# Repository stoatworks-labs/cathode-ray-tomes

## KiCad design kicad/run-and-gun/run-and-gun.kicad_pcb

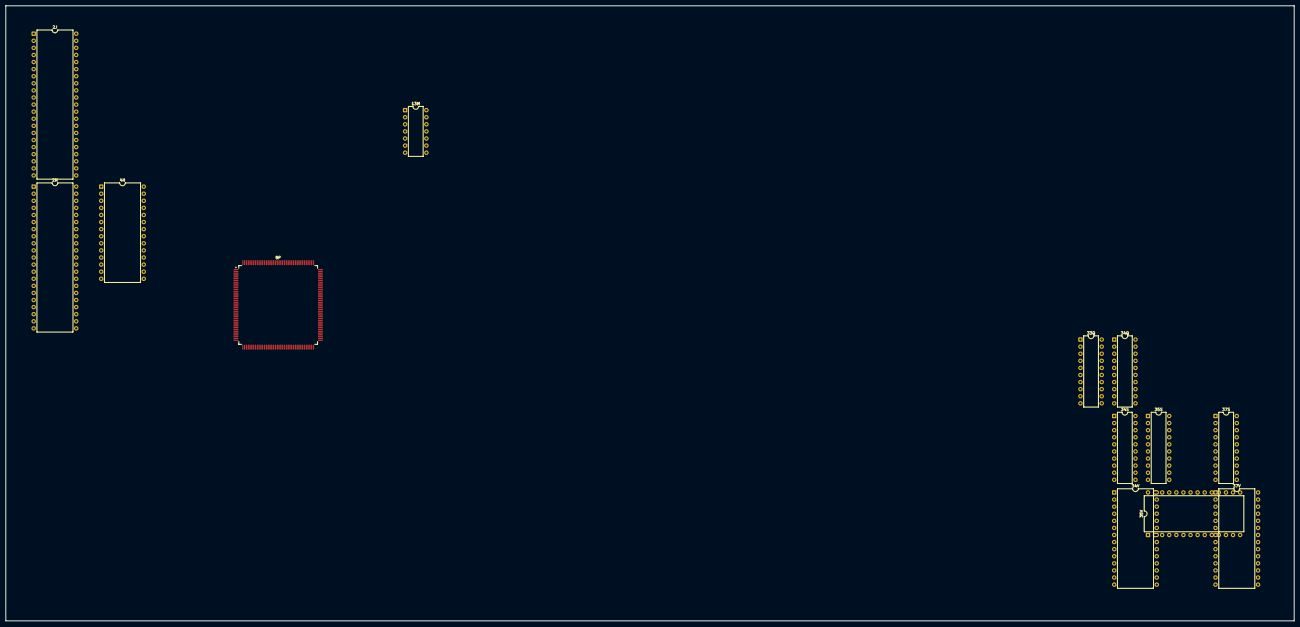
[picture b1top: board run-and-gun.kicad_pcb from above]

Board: 2 copper layers, 461.7 x 220.4 mm, 13 parts (0 on the bottom side), 98 nets, no tracks yet.

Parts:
2J, 2N: HN624116P; DIP-42_W15.24mm
4N: HM62256BLP; DIP-28_W15.24mm
8P: 054539; PQFP-160_28x28mm_P0.65mm
13M: 74LS04; DIP-14_W7.62mm
33Q: 74LS273; DIP-20_W7.62mm
34Q: 74LS244; DIP-20_W7.62mm
34S, 35S, 37S: 74LS245; DIP-20_W7.62mm
34V, 35V, 37V: CXK58257ASP-70L; DIP-28_W15.24mm

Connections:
/PSAC/A0: 34V.10, 35V.10, 37V.10
/PSAC/A1: 34V.9, 35V.9, 37V.9
/PSAC/A2: 34V.8, 35V.8, 37V.8
/PSAC/A3: 34V.7, 35V.7, 37V.7
/PSAC/A4: 34V.6, 35V.6, 37V.6
/PSAC/A5: 34V.5, 35V.5, 37V.5
/PSAC/A6: 34V.4, 35V.4, 37V.4
/PSAC/A7: 34V.3, 35V.3, 37V.3
/PSAC/A8: 34V.25, 35V.25, 37V.25
/PSAC/A9: 34V.24, 35V.24, 37V.24
/PSAC/A10: 34V.21, 35V.21, 37V.21
/PSAC/A11: 34V.23, 35V.23, 37V.23
/PSAC/A12: 34V.2, 35V.2, 37V.2
/PSAC/A13: 34V.26, 35V.26, 37V.26
/PSAC/A14: 34V.1, 35V.1, 37V.1
/PSAC/DIR: 34S.1, 35S.1, 37S.1
/PSAC/VDD: 34V.28, 35V.28, 37V.28
/PSAC/VSS: 34V.14, 35V.14, 37V.14
/PSAC/X0: 33Q.4, 34Q.2
/PSAC/X1: 33Q.8, 34Q.4
/PSAC/X2: 33Q.14, 34Q.6
/PSAC/X3: 33Q.18, 34Q.8
/PSAC/X4: 33Q.3, 34Q.11
/PSAC/X5: 33Q.7, 34Q.13
/PSAC/X6: 33Q.13, 34Q.15
/PSAC/X7: 33Q.17, 34Q.17
/PSAC/~CS: 34V.20, 35V.20, 37V.20
/PSAC/~OE: 34V.22, 35V.22, 37V.22
/pcm/K054539/RAMR~W: 4N.27, 8P.107
/pcm/K054539/RAM~CE: 4N.20, 8P.109
/pcm/K054539/RAM~OE: 4N.22, 8P.108
/pcm/K054539/ROM~CE: 2J.11, 2N.11, 8P.133
/pcm/K054539/ROM~OE: 2N.13, 8P.131, 13M.11
/pcm/K054539/R_A0: 2N.30, 4N.10, 8P.132
/pcm/K054539/R_A1: 2J.10, 2N.10, 4N.9, 8P.135
/pcm/K054539/R_A2: 2J.9, 2N.9, 4N.8, 8P.137
/pcm/K054539/R_A3: 2J.8, 2N.8, 4N.7, 8P.141
/pcm/K054539/R_A4: 2J.7, 2N.7, 4N.6, 8P.143
/pcm/K054539/R_A5: 2J.6, 2N.6, 4N.5, 8P.146
/pcm/K054539/R_A6: 2J.5, 2N.5, 4N.4, 8P.148
/pcm/K054539/R_A7: 2J.4, 2N.4, 4N.3, 8P.151
/pcm/K054539/R_A8: 2J.3, 2N.3, 4N.25, 8P.153
/pcm/K054539/R_A9: 2J.41, 2N.41, 4N.24, 8P.157
/pcm/K054539/R_A10: 2J.40, 2N.40, 4N.21, 8P.154
/pcm/K054539/R_A11: 2J.39, 2N.39, 4N.23, 8P.152
/pcm/K054539/R_A12: 2J.38, 2N.38, 4N.2, 8P.149
/pcm/K054539/R_A13: 2J.37, 2N.37, 4N.26, 8P.147
/pcm/K054539/R_A14: 2J.36, 2N.36, 8P.144
/pcm/K054539/R_A15: 2J.35, 2N.35, 8P.142
/pcm/K054539/R_A16: 2J.34, 2N.34, 4N.1, 8P.138
/pcm/K054539/R_A17: 2J.33, 2N.33, 8P.136
/pcm/K054539/R_A18: 2J.2, 2N.2, 8P.156
/pcm/K054539/R_A19: 2J.1, 2N.1, 8P.158
/pcm/K054539/R_A20: 2J.42, 2N.42, 8P.159
/pcm/K054539/R_D0: 2J.14, 2N.14, 4N.11, 8P.128
/pcm/K054539/R_D1: 2J.16, 2N.16, 4N.12, 8P.126
/pcm/K054539/R_D2: 2J.18, 2N.18, 4N.13, 8P.124
/pcm/K054539/R_D3: 2J.20, 2N.20, 4N.15, 8P.122
/pcm/K054539/R_D4: 2J.23, 2N.23, 4N.16, 8P.123
/pcm/K054539/R_D5: 2J.25, 2N.25, 4N.17, 8P.125
/pcm/K054539/R_D6: 2J.27, 2N.27, 4N.18, 8P.127
/pcm/K054539/R_D7: 2J.29, 2N.29, 4N.19, 8P.129
GND: 33Q.10, 34Q.10
unnamed: 2J.13, 13M.10
unnamed: 34Q.18, 37S.2
unnamed: 34Q.9, 37S.6
unnamed: 34Q.16, 37S.3
unnamed: 34Q.7, 37S.7
unnamed: 34Q.14, 37S.4
unnamed: 34Q.5, 37S.8
unnamed: 34Q.12, 37S.5
unnamed: 34Q.3, 37S.9
unnamed: 34S.18, 34V.11
unnamed: 34S.17, 34V.12
unnamed: 34S.16, 34V.13
unnamed: 34S.15, 34V.15
unnamed: 34S.14, 34V.16
unnamed: 34S.13, 34V.17
unnamed: 34S.12, 34V.18
unnamed: 34S.11, 34V.19
unnamed: 35S.18, 35V.11
unnamed: 35S.17, 35V.12
unnamed: 35S.16, 35V.13
unnamed: 35S.15, 35V.15
unnamed: 35S.14, 35V.16
unnamed: 35S.13, 35V.17
unnamed: 35S.12, 35V.18
unnamed: 35S.11, 35V.19
unnamed: 37S.18, 37V.11
unnamed: 37S.17, 37V.12
unnamed: 37S.16, 37V.13
unnamed: 37S.15, 37V.15
unnamed: 37S.14, 37V.16
unnamed: 37S.13, 37V.17
unnamed: 37S.12, 37V.18
unnamed: 37S.11, 37V.19
VCC: 2J.22, 2N.22, 4N.28, 8P.20, 8P.40, 8P.56, 8P.60, 8P.73, 8P.80, 8P.100, 8P.120, 8P.140, 8P.160, 33Q.20, 34Q.20
VSS: 2J.12, 2J.31, 2J.32, 2N.12, 2N.31, 2N.32, 8P.1, 8P.10, 8P.30, 8P.41, 8P.50, 8P.57, 8P.59, 8P.61, 8P.62, 8P.65, 8P.66, 8P.70, 8P.72, 8P.74, 8P.81, 8P.90, 8P.110, 8P.121, 8P.130, 8P.139, 8P.150

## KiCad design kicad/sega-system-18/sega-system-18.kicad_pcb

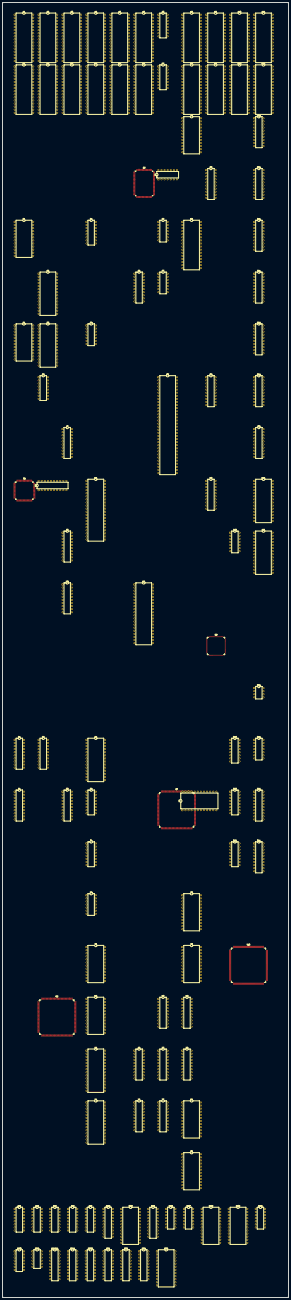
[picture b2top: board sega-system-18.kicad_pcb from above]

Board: 2 copper layers, 235.2 x 1065.0 mm, 114 parts (0 on the bottom side), 662 nets, no tracks yet.

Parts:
A1, A2, A3, A5, A6, A8, A9, A10, A11: 27C020; DIP-32_W15.24mm
A4: 27C010; DIP-32_W15.24mm
A7: 2501; DIP-16_W7.62mm
AA4, AA5, AA6, AA8, AA9: 2501; DIP-16_W7.62mm
AA11: 74LS245; DIP-20_W7.62mm
B1, B2, B3, B4, B5, B6, B8, B9, B10, B11: 27C020; DIP-32_W15.24mm
B7: 74LS139; DIP-16_W7.62mm
BB8: HM6116P-3; DIP-24_W15.24mm
BB9: 74LS245; DIP-20_W7.62mm
C8: HM6116P-3; DIP-24_W15.24mm
C11: 74LS244; DIP-20_W7.62mm
D6: 315_5296; PQFP-100_14x20mm_P0.65mm
D7: 74LS08; DIP-14_W7.62mm
D9: 74LS245; DIP-20_W7.62mm
D11: 74LS244; DIP-20_W7.62mm
E1: YM3438; DIP-24_W15.24mm
E4: 74LS157; DIP-16_W7.62mm
E7: 7400; DIP-14_W7.62mm
E8: 315-5242; DIP-32_W15.24mm
E11: 74LS374; DIP-20_W7.62mm
F2: HM65256B_SERIES; DIP-28_W15.24mm
F6: 74LS273; DIP-20_W7.62mm
F7: 74LS32; DIP-14_W7.62mm
F11: 74LS374; DIP-20_W7.62mm
G1: YM3438; DIP-24_W15.24mm
G2: HM65256B_SERIES; DIP-28_W15.24mm
G4: 74LS32; DIP-14_W7.62mm
G11: 74LS244; DIP-20_W7.62mm
H2: 74LS139; DIP-16_W7.62mm
H7: 68000D; DIP-64_W15.24mm
H9: 74LS245; DIP-20_W7.62mm
H11: 74LS244; DIP-20_W7.62mm
IC66, IC67: 74HC4066; DIP-14_W7.62mm
IC69, IC70: MB8461-12; DIP-24_W15.24mm
IC92, IC93: TL084; DIP-14_W7.62mm
IC94: MB3733-31; DIP-12_W7.62mm
J3: PAL16L8; DIP-20_W7.62mm
J11: 74LS244; DIP-20_W7.62mm
K1: ASSP5C68A; PQFP-80_14x14mm_P0.65mm
K2, K9: 74LS245; DIP-20_W7.62mm
K4: Z80CPU; DIP-40_W15.24mm
K11: MB8464A-10L-LL; DIP-28_W15.24mm
L3: 74LS244; DIP-20_W7.62mm
L10: 74LS74; DIP-14_W7.62mm
L11: MB8464A-10L-LL; DIP-28_W15.24mm
M3: 74LS244; DIP-20_W7.62mm
M6: D8751H-8; DIP-40_W15.24mm
N9: 315-5360; TQFP-120_14x14mm_P0.4mm
P11: MB3771; DIP-8_W7.62mm
PALR11: PAL16R6; DIP-20_W7.62mm
PD11: PLUS153DN; DIP-20_W7.62mm
PRR8: PAL16L8; DIP-20_W7.62mm
Q1, Q2: 74LS244; DIP-20_W7.62mm
Q4: TMM2063AP_10; DIP-28_W15.24mm
Q10: 74F367; DIP-16_W7.62mm
Q11: 74LS74; DIP-14_W7.62mm
RR1, RR2: 74LS374; DIP-20_W7.62mm
RR4: 74LS273; DIP-20_W7.62mm
RR8: CY7C128-45PC; DIP-24_W15.24mm
S1: 74LS373; DIP-20_W7.62mm
S3: 74LS374; DIP-20_W7.62mm
S4: 74LS157; DIP-16_W7.62mm
S7: 315-5361; PQFP-160_28x28mm_P0.65mm
S8: CY7C128-45PC; DIP-24_W15.24mm
S10: 74F163; DIP-16_W7.62mm
S11: PAL16L8; DIP-20_W7.62mm
T4: 74LS157; DIP-16_W7.62mm
T10: 74F163; DIP-16_W7.62mm
T11: PAL16L8; DIP-20_W7.62mm
U4: 74LS74; DIP-14_W7.62mm
U8: CY7C128-45PC; DIP-24_W15.24mm
V4: HM6116P-3; DIP-24_W15.24mm
V8: CY7C128-45PC; DIP-24_W15.24mm
V10: 315-5313; PQFP-128_28x28mm_P0.8mm
W2: 315-5362; PQFP-160_28x28mm_P0.65mm
W4: HM6116P-3; DIP-24_W15.24mm
W7: 74LS245; DIP-20_W7.62mm
W8: 74LS244; DIP-20_W7.62mm
X4: HM65256B_SERIES; DIP-28_W15.24mm
X6, X8: 74LS244; DIP-20_W7.62mm
X7: 74LS245; DIP-20_W7.62mm
Y4: HM65256B_SERIES; DIP-28_W15.24mm
Y6, Y7: 74LS244; DIP-20_W7.62mm
Y8: CY7C128-45PC; DIP-24_W15.24mm
Z8: CY7C128-45PC; DIP-24_W15.24mm

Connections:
/BUFFOBJ~OE: W8.1, W8.19, X8.1, X8.19
/BUFFSH_A->B: S7.159, W7.1, X7.1
/CLK8: D6.85, E1.24, E7.9, E7.10, G1.24, K4.6, M6.19, Q10.10, Q11.5, U4.3
/COLA0: BB8.8, C8.8, C11.5, W2.58
/COLA1: BB8.7, C8.7, C11.7, W2.57
/COLA2: BB8.6, C8.6, C11.3, W2.56
/COLA3: BB8.5, C8.5, D11.18, W2.54
/COLA4: BB8.4, C8.4, D11.16, W2.53
/COLA5: BB8.3, C8.3, D11.14, W2.52
/COLA6: BB8.2, C8.2, D11.12, W2.51
/COLA7: BB8.1, C8.1, D11.9, W2.49
/COLA8: BB8.23, C8.23, D11.7, W2.48
/COLA9: BB8.22, C8.22, D11.5, W2.47
/COLA10: BB8.19, C8.19, D11.3, W2.46
/Color Mixer/COLAD0: C8.9, D9.11, E8.10
/Color Mixer/COLAD1: C8.10, D9.12, E8.11
/Color Mixer/COLAD2: C8.11, D9.13, E8.12
/Color Mixer/COLAD3: C8.13, D9.14, E8.13
/Color Mixer/COLAD4: C8.14, D9.15, E8.23
/Color Mixer/COLAD5: C8.15, D9.16, E8.22
/Color Mixer/COLAD6: C8.16, D9.17, E8.21
/Color Mixer/COLAD7: C8.17, D9.18, E8.20
/Color Mixer/COLAD8: BB8.9, BB9.11, E8.4
/Color Mixer/COLAD9: BB8.10, BB9.12, E8.5
/Color Mixer/COLAD10: BB8.11, BB9.13, E8.6
/Color Mixer/COLAD11: BB8.13, BB9.14, E8.7
/Color Mixer/COLAD12: BB8.14, BB9.15, E8.9
/Color Mixer/COLAD13: BB8.15, BB9.16, E8.25
/Color Mixer/COLAD14: BB8.16, BB9.17, E8.3
/Color Mixer/COLAD15: BB8.17, BB9.18
/Color Mixer/S18B: E8.31, IC66.8
/Color Mixer/S18G: E8.18, IC66.4
/Color Mixer/S18R: E8.15, IC66.1
/Color Mixer/video_mux/OBJPRIO0': E11.5, PD11.7
/Color Mixer/video_mux/OBJPRIO1': F11.19, PD11.6
/Color Mixer/video_mux/PRIO0: F6.2, PD11.17
/Color Mixer/video_mux/PRIO1: F6.5, PD11.16
/Color Mixer/video_mux/PRIO2: F6.6, PD11.15
/Color Mixer/video_mux/PRIO3: F6.9, PD11.14
/Color Mixer/video_mux/TILEMAP0': F11.5, PD11.3
/Color Mixer/video_mux/TILEMAP1': F11.9, PD11.4
/Color Mixer/video_mux/TILEMAP3': E11.9, PD11.8
/Color Mixer/video_mux/TILEMAP4': E11.15, PD11.9
/Color Mixer/video_mux/VDP_SEL: IC67.5, IC67.6, IC67.12, IC67.13, PD11.18
/Color Mixer/video_mux/~SA': F11.15, PD11.5
/Color Mixer/video_mux/~VDP_SEL: IC66.5, IC66.6, IC66.12, IC66.13, PD11.19
/Color Mixer/~WR_H: C8.21, C11.9
/Color Mixer/~WR_L: BB8.21, C11.12
/DC_SND~CS: K1.77, PRR8.4
/EDCK: PALR11.18, V10.53
/FC0: H7.28, N9.116
/FC1: H7.27, N9.115
/FLIP: D6.3, PRR8.6, S7.158, W2.128
/IO Controller/GPIO0: AA11.2, D6.33
/IO Controller/GPIO1: AA11.3, D6.32
/IO Controller/GPIO2: AA11.4, D6.31
/IO Controller/GPIO3: AA11.5, D6.30
/IO Controller/GPIO4: AA11.6, D6.29
/IO Controller/GPIO5: AA11.7, D6.28
/IO Controller/GPIO6: AA11.8, D6.27
/IO Controller/GPIO7: AA11.9, D6.26
/IO Controller/IO_1P_BTN_1: AA8.14, D6.17
/IO Controller/IO_1P_BTN_2: AA8.16, D6.18
/IO Controller/IO_1P_BTN_3: AA8.12, D6.19
/IO Controller/IO_1P_BTN_4: AA8.10, D6.20
/IO Controller/IO_1P_DOWN: AA9.16, D6.21
/IO Controller/IO_1P_LEFT: AA9.12, D6.24
/IO Controller/IO_1P_RIGHT: AA9.10, D6.23
/IO Controller/IO_1P_UP: AA9.14, D6.22
/IO Controller/IO_2P_BTN_1: AA6.14, D6.7
/IO Controller/IO_2P_BTN_2: AA6.16, D6.8
/IO Controller/IO_2P_BTN_3: AA6.12, D6.9
/IO Controller/IO_2P_BTN_4: AA6.10, D6.10
/IO Controller/IO_2P_DOWN: A7.16, D6.11
/IO Controller/IO_2P_LEFT: A7.12, D6.14
/IO Controller/IO_2P_RIGHT: A7.10, D6.13
/IO Controller/IO_2P_UP: A7.14, D6.12
/IO Controller/IO_A-B: AA11.1, D6.34
/IO Controller/IO_DRIVER1: D6.86, F7.4, F7.9
/IO Controller/SCRA_A15: D6.88, E4.2
/IO Controller/SCRA_A16: D6.89, E4.5
/IO Controller/SCRA_A17: D6.93, E4.11
/IO Controller/SCRA_A18: D6.92, E4.14
/IO Controller/SCRB_A15: D6.94, E4.3
/IO Controller/SCRB_A16: D6.95, E4.6
/IO Controller/SCRB_A17: D6.97, E4.10
/IO Controller/SCRB_A18: D6.96, E4.13
/IO Controller/~AB12: E7.11, F7.10
/IO_1P_SELECT: AA5.12, D6.44, M6.8
/IO_1P_START: AA5.14, D6.42, M6.6
/IO_2P_SELECT: AA5.10, D6.43, M6.7
/IO_2P_START: AA5.16, D6.39, M6.5
/IO_COIN_1: AA4.14, D6.35, M6.1
/IO_COIN_2: AA4.16, D6.36, M6.2
/IO_COIN_3: AA4.12, D6.37, M6.3
/IO_SERVICE: AA4.10, D6.38, M6.4
/MAIN_A1: C11.15, G11.8, H7.29, N9.6
/MAIN_A2: C11.13, G11.13, H7.30, N9.7
/MAIN_A3: C11.17, G11.6, H7.31, N9.8
/MAIN_A4: D11.2, G11.15, H7.32, N9.9
/MAIN_A5: D11.4, G11.4, H7.33, N9.10
/MAIN_A6: D11.6, G11.17, H7.34, N9.11
/MAIN_A7: D11.8, G11.2, H7.35, N9.12
/MAIN_A8: D11.11, H7.36, H11.11, N9.13
/MAIN_A9: D11.13, H7.37, H11.8, N9.16
/MAIN_A10: D11.15, H7.38, H11.13, N9.17
/MAIN_A11: D11.17, H7.39, H11.6, N9.18
/MAIN_A12: H7.40, H11.15, N9.19
/MAIN_A13: H7.41, H11.4, N9.20
/MAIN_A14: H7.42, H11.17, N9.21
/MAIN_A15: H7.43, H11.2, N9.22
/MAIN_A16: H7.44, J11.11, N9.23
/MAIN_A17: H7.45, J11.8, N9.5
/MAIN_A18: H7.46, J11.13, N9.4
/MAIN_A19: H7.47, J11.6, N9.3
/MAIN_A20: H7.48, J11.15, N9.2
/MAIN_A21: H7.50, J11.4, N9.119
/MAIN_A22: H7.51, J11.17, N9.118
/MAIN_A23: H7.52, J11.2, N9.117
/MAIN_AB1: A5.12, A6.12, D6.81, G11.12, K11.10, L11.10, S7.1, V10.71, Y6.2
/MAIN_AB2: A5.11, A6.11, D6.80, G11.7, K11.9, L11.9, S7.2, V10.72, Y6.4
/MAIN_AB3: A5.10, A6.10, D6.79, G11.14, K11.8, L11.8, V10.73, Y6.6, Y7.8
/MAIN_AB4: A5.9, A6.9, D6.78, G11.5, K11.7, L11.7, V10.74, Y6.8, Y7.11
/MAIN_AB5: A5.8, A6.8, D6.77, G11.16, K11.6, L11.6, V10.75, Y6.17, Y7.6
/MAIN_AB6: A5.7, A6.7, G11.3, K11.5, L11.5, V10.76, Y6.15, Y7.13
/MAIN_AB7: A5.6, A6.6, G11.18, K11.4, L11.4, V10.77, Y6.13, Y7.4
/MAIN_AB8: A5.5, A6.5, H11.9, K11.3, L11.3, V10.78, Y6.11, Y7.15
/MAIN_AB9: A5.27, A6.27, H11.12, K11.25, L11.25, V10.79, X6.11, Y7.2
/MAIN_AB10: A5.26, A6.26, H11.7, K11.24, L11.24, V10.80, X6.13, Y7.17
/MAIN_AB11: A5.23, A6.23, H11.14, K11.21, L11.21, V10.81, X6.15
/MAIN_AB12: A5.25, A6.25, E7.13, F7.5, H11.5, K11.23, L11.23, V10.82, X6.8
/MAIN_AB13: A5.4, A6.4, D6.62, H11.16, K11.2, L11.2, V10.83, X6.6
/MAIN_AB14: A5.28, A6.28, H11.3, V10.84, X6.4
/MAIN_AB15: A5.29, A6.29, H11.18, V10.85, X6.2
/MAIN_AB16: A5.3, A6.3, J11.9, V10.86, W2.152
/MAIN_AB17: A5.2, A6.2, J11.12, V10.87
/MAIN_AB18: A5.30, A6.30, J11.7, V10.88
/MAIN_AB19: J11.14, V10.89
/MAIN_AB20: J11.5, V10.90
/MAIN_AB21: J11.16, V10.91
/MAIN_AB22: J11.3, V10.92
/MAIN_AB23: J11.18, V10.93
/MAIN_CLK: H7.15, K1.70, L10.5, N9.106, Q10.6, V10.49
/MAIN_D0: D9.9, F6.3, H7.5, H9.2, N9.76, Q1.11, RR1.12
/MAIN_D1: D9.8, F6.4, H7.4, H9.3, N9.77, Q1.8, RR1.9
/MAIN_D2: D9.7, F6.7, H7.3, H9.4, N9.78, Q1.13, RR1.15
/MAIN_D3: D9.6, F6.8, H7.2, H9.5, N9.79, Q1.6, RR1.6
/MAIN_D4: D9.5, F6.13, H7.1, H9.6, N9.80, Q1.15, RR1.16
/MAIN_D5: D9.4, F6.14, H7.64, H9.7, N9.81, Q1.4, RR1.5
/MAIN_D6: D9.3, F6.17, H7.63, H9.8, N9.82, Q1.17, RR1.19
/MAIN_D7: D9.2, F6.18, H7.62, H9.9, N9.83, Q1.2, RR1.2
/MAIN_D8: BB9.9, H7.61, K9.2, N9.86, Q2.11, RR2.12
/MAIN_D9: BB9.8, H7.60, K9.3, N9.87, Q2.8, RR2.9
/MAIN_D10: BB9.7, H7.59, K9.4, N9.88, Q2.13, RR2.15
/MAIN_D11: BB9.6, H7.58, K9.5, N9.89, Q2.6, RR2.6
/MAIN_D12: BB9.5, H7.57, K9.6, N9.90, Q2.15, RR2.16
/MAIN_D13: BB9.4, H7.56, K9.7, N9.92, Q2.4, RR2.5
/MAIN_D14: BB9.3, H7.55, K9.8, N9.93, Q2.17, RR2.19
/MAIN_D15: BB9.2, H7.54, K9.9, N9.94, Q2.2, RR2.2
/MAIN_DB0: A5.13, D6.74, H9.18, L11.11, V10.55, X7.2
/MAIN_DB1: A5.14, D6.73, H9.17, L11.12, V10.56, X7.3
/MAIN_DB2: A5.15, D6.72, H9.16, L11.13, V10.57, X7.4
/MAIN_DB3: A5.17, D6.71, H9.15, L11.15, V10.58, X7.5
/MAIN_DB4: A5.18, D6.70, H9.14, L11.16, V10.59, X7.6
/MAIN_DB5: A5.19, D6.69, H9.13, L11.17, V10.60, X7.7
/MAIN_DB6: A5.20, D6.68, H9.12, L11.18, V10.61, X7.8
/MAIN_DB7: A5.21, D6.67, H9.11, L11.19, V10.62, X7.9
/MAIN_DB8: A6.13, K9.18, K11.11, V10.63, W7.2
/MAIN_DB9: A6.14, K9.17, K11.12, V10.64, W7.3
/MAIN_DB10: A6.15, K9.16, K11.13, V10.65, W7.4
/MAIN_DB11: A6.17, K9.15, K11.15, V10.66, W7.5
/MAIN_DB12: A6.18, K9.14, K11.16, V10.67, W7.6
/MAIN_DB13: A6.19, K9.13, K11.17, V10.68, W7.7
/MAIN_DB14: A6.20, K9.12, K11.18, V10.69, W7.8
/MAIN_DB15: A6.21, K9.11, K11.19, V10.70, W7.9
/MAIN_R~W: H7.9, N9.99, V10.113
/MAIN_~CE: A5.22, A6.22, N9.70
/MAIN_~OE: A5.24, A6.24, D6.82, K11.22, L11.22, N9.41
/MAIN_~RD: BB9.1, D6.84, D9.1, H9.1, K9.1, N9.49
/MAIN_~WR: D6.83, F7.2, L11.27
/MAIN~HALT: H7.17, N9.107
/MAIN~RST: H7.18, N9.108
/MAPP2MAIN~WE: K11.27, N9.42
/MMAP_~DRI5: N9.47, W2.148
/MegaDrive VDP/A0: IC69.23, IC70.23
/MegaDrive VDP/A1: IC69.22, IC70.22
/MegaDrive VDP/A2: IC69.21, IC70.21
/MegaDrive VDP/A3: IC69.20, IC70.20
/MegaDrive VDP/A4: IC69.17, IC70.17
/MegaDrive VDP/A5: IC69.16, IC70.16
/MegaDrive VDP/A6: IC69.15, IC70.15
/MegaDrive VDP/A7: IC69.19, IC70.19
/MegaDrive VDP/AD0: IC69.11, V10.31
/MegaDrive VDP/AD1: IC69.12, V10.32
/MegaDrive VDP/AD2: IC69.1, V10.33
/MegaDrive VDP/AD3: IC69.2, V10.34
/MegaDrive VDP/AD4: IC70.11, V10.35
/MegaDrive VDP/AD5: IC70.12, V10.36
/MegaDrive VDP/AD6: IC70.1, V10.37
/MegaDrive VDP/AD7: IC70.2, V10.38
/MegaDrive VDP/~CAS: IC69.24, IC70.24
/MegaDrive VDP/~OE1: IC69.10, IC70.10, V10.16
/MegaDrive VDP/~RAS: IC69.14, IC70.14
/MegaDrive VDP/~SC: IC69.7, IC70.7, V10.11
/MegaDrive VDP/~SE0: IC69.3, IC70.3, V10.10
/MegaDrive VDP/~WE0: IC69.13, IC70.13, V10.15
/Memory Mapper/INT1: M6.13, N9.51
/Memory Mapper/PO_0: M6.39, N9.52
/Memory Mapper/PO_1: M6.38, N9.53
/Memory Mapper/PO_2: M6.37, N9.54
/Memory Mapper/PO_3: M6.36, N9.55
/Memory Mapper/PO_4: M6.35, N9.56
/Memory Mapper/PO_5: M6.34, N9.57
/Memory Mapper/PO_6: M6.33, N9.58
/Memory Mapper/PO_7: M6.32, N9.59
/Memory Mapper/UCRST: M6.9, Q11.8
/OBJCOL0: S7.79, W2.31
/OBJCOL1: S7.78, W2.32
/OBJCOL2: S7.77, W2.33
/OBJCOL3: S7.76, W2.34
/OBJCOL4: S7.75, W2.36
/OBJCOL5: S7.74, W2.37
/OBJCOL6: S7.73, W2.38
/OBJCOL7: S7.72, W2.39
/OBJCOL8: S7.71, W2.42
/OBJCOL9: S7.69, W2.43
/OBJCOL10: E11.3, S7.68, W2.44
/OBJCOL11: F11.17, S7.66, W2.45
/OBJCOL~UK0: S7.156, W2.153
/OBJCOL~UK1: S7.157, W2.154
/OBJ_A0: A8.12, A9.12, A10.12, A11.12, B8.12, B9.12, B10.12, B11.12, X8.9
/OBJ_A1: A8.11, A9.11, A10.11, A11.11, B8.11, B9.11, B10.11, B11.11, X8.12
/OBJ_A2: A8.10, A9.10, A10.10, A11.10, B8.10, B9.10, B10.10, B11.10, X8.7
/OBJ_A3: A8.9, A9.9, A10.9, A11.9, B8.9, B9.9, B10.9, B11.9, X8.14
/OBJ_A4: A8.8, A9.8, A10.8, A11.8, B8.8, B9.8, B10.8, B11.8, X8.5
/OBJ_A5: A8.7, A9.7, A10.7, A11.7, B8.7, B9.7, B10.7, B11.7, X8.16
/OBJ_A6: A8.6, A9.6, A10.6, A11.6, B8.6, B9.6, B10.6, B11.6, X8.3
/OBJ_A7: A8.5, A9.5, A10.5, A11.5, B8.5, B9.5, B10.5, B11.5, X8.18
/OBJ_A8: A8.27, A9.27, A10.27, A11.27, B8.27, B9.27, B10.27, B11.27, W8.9
/OBJ_A9: A8.26, A9.26, A10.26, A11.26, B8.26, B9.26, B10.26, B11.26, W8.12
/OBJ_A10: A8.23, A9.23, A10.23, A11.23, B8.23, B9.23, B10.23, B11.23, W8.7
/OBJ_A11: A8.25, A9.25, A10.25, A11.25, B8.25, B9.25, B10.25, B11.25, W8.14
/OBJ_A12: A8.4, A9.4, A10.4, A11.4, B8.4, B9.4, B10.4, B11.4, W8.5
/OBJ_A13: A8.28, A9.28, A10.28, A11.28, B8.28, B9.28, B10.28, B11.28, W8.16
/OBJ_A14: A8.29, A9.29, A10.29, A11.29, B8.29, B9.29, B10.29, B11.29, W8.3
/OBJ_A15: A8.3, A9.3, A10.3, A11.3, B8.3, B9.3, B10.3, B11.3, W8.18
/OBJ_D0: B8.13, B9.13, B10.13, B11.13, S7.81
/OBJ_D1: B8.14, B9.14, B10.14, B11.14, S7.82
/OBJ_D2: B8.15, B9.15, B10.15, B11.15, S7.83
/OBJ_D3: B8.17, B9.17, B10.17, B11.17, S7.84
/OBJ_D4: B8.18, B9.18, B10.18, B11.18, S7.85
/OBJ_D5: B8.19, B9.19, B10.19, B11.19, S7.86
/OBJ_D6: B8.20, B9.20, B10.20, B11.20, S7.87
/OBJ_D7: B8.21, B9.21, B10.21, B11.21, S7.89
/OBJ_D8: A8.13, A9.13, A10.13, A11.13, S7.91
/OBJ_D9: A8.14, A9.14, A10.14, A11.14, S7.92
/OBJ_D10: A8.15, A9.15, A10.15, A11.15, S7.93
/OBJ_D11: A8.17, A9.17, A10.17, A11.17, S7.95
/OBJ_D12: A8.18, A9.18, A10.18, A11.18, S7.96
/OBJ_D13: A8.19, A9.19, A10.19, A11.19, S7.98
/OBJ_D14: A8.20, A9.20, A10.20, A11.20, S7.99
/OBJ_D15: A8.21, A9.21, A10.21, A11.21, S7.101
/PCM_~CE0: B4.22, H2.5
/PCM_~CE1: B5.22, H2.6
/PCM_~CE2: B6.22, H2.7
/ROM board/OBJ_MSB0: A8.2, A9.2, A10.2, A11.2, B8.2, B9.2, B10.2, B11.2
/ROM board/OBJ_MSB1: A8.30, A9.30, A10.30, A11.30, B8.30, B9.30, B10.30, B11.30
/ROM board/PCM_SNDROM: B4.30, B5.30, B6.30
/ROM board/SCR_MSB: A1.30, A2.30, A3.30, B1.30, B2.30, B3.30
/ROM board/SCR_~OE: A1.2, A1.24, A2.2, A2.24, A3.2, A3.24, B1.2, B2.2, B3.2
/ROM board/cpurom/SND_AB0: A4.12, B4.12, B5.12, B6.12
/ROM board/cpurom/SND_AB1: A4.11, B4.11, B5.11, B6.11
/ROM board/cpurom/SND_AB2: A4.10, B4.10, B5.10, B6.10
/ROM board/cpurom/SND_AB3: A4.9, B4.9, B5.9, B6.9
/ROM board/cpurom/SND_AB4: A4.8, B4.8, B5.8, B6.8
/ROM board/cpurom/SND_AB5: A4.7, B4.7, B5.7, B6.7
/ROM board/cpurom/SND_AB6: A4.6, B4.6, B5.6, B6.6
/ROM board/cpurom/SND_AB7: A4.5, B4.5, B5.5, B6.5
/ROM board/cpurom/SND_AB8: A4.27, B4.27, B5.27, B6.27
/ROM board/cpurom/SND_AB9: A4.26, B4.26, B5.26, B6.26
/ROM board/cpurom/SND_AB10: A4.23, B4.23, B5.23, B6.23
/ROM board/cpurom/SND_AB11: A4.25, B4.25, B5.25, B6.25
/ROM board/cpurom/SND_AB12: A4.4, B4.4, B5.4, B6.4
/ROM board/cpurom/SND_AB13: A4.28, B4.28, B5.28, B6.28
/ROM board/cpurom/SND_AB14: A4.29, B4.29, B5.29, B6.29
/ROM board/cpurom/SND_AB15: A4.3, B4.3, B5.3, B6.3
/ROM board/cpurom/SND_AB16: A4.24, B4.2, B5.2, B6.2
/ROM board/objrom/OBJ_~CE0: A11.22, B7.4, B11.22
/ROM board/objrom/OBJ_~CE1: A9.22, B7.5, B9.22
/ROM board/objrom/OBJ_~CE2: A10.22, B7.6, B10.22
/ROM board/objrom/OBJ_~CE3: A8.22, B7.7, B8.22
/ROM board/scrrom/SCR_~CE0: B1.22, B2.22, B3.22, B7.12
/ROM board/scrrom/SCR_~CE1: A1.22, A2.22, A3.22, B7.11
/S16B Ojects/BUFFSH~CE: S7.9, W7.19, X7.19, Y7.1, Y7.19
/S16B Ojects/LBUFA_A0: RR8.8, S7.102, S8.8
/S16B Ojects/LBUFA_A1: RR8.7, S7.103, S8.7
/S16B Ojects/LBUFA_A2: RR8.6, S7.105, S8.6
/S16B Ojects/LBUFA_A3: RR8.5, S7.106, S8.5
/S16B Ojects/LBUFA_A4: RR8.4, S7.108, S8.4
/S16B Ojects/LBUFA_A5: RR8.3, S7.109, S8.3
/S16B Ojects/LBUFA_A6: RR8.2, S7.111, S8.2
/S16B Ojects/LBUFA_A7: RR8.1, S7.112, S8.1
/S16B Ojects/LBUFA_A8: RR8.23, S7.114, S8.23
/S16B Ojects/LBUFA_D0: RR8.9, S7.115
/S16B Ojects/LBUFA_D1: RR8.10, S7.116
/S16B Ojects/LBUFA_D2: RR8.11, S7.117
/S16B Ojects/LBUFA_D3: RR8.13, S7.118
/S16B Ojects/LBUFA_D4: RR8.14, S7.119
/S16B Ojects/LBUFA_D5: RR8.15, S7.120
/S16B Ojects/LBUFA_D6: RR8.16, S7.121
/S16B Ojects/LBUFA_D7: RR8.17, S7.122
/S16B Ojects/LBUFA_D8: S7.123, S8.9
/S16B Ojects/LBUFA_D9: S7.124, S8.10
/S16B Ojects/LBUFA_D10: S7.125, S8.11
/S16B Ojects/LBUFA_D11: S7.126, S8.13
/S16B Ojects/LBUFB_A0: S7.15, U8.8, V8.8
/S16B Ojects/LBUFB_A1: S7.16, U8.7, V8.7
/S16B Ojects/LBUFB_A2: S7.18, U8.6, V8.6
/S16B Ojects/LBUFB_A3: S7.19, U8.5, V8.5
/S16B Ojects/LBUFB_A4: S7.21, U8.4, V8.4
/S16B Ojects/LBUFB_A5: S7.22, U8.3, V8.3
/S16B Ojects/LBUFB_A6: S7.23, U8.2, V8.2
/S16B Ojects/LBUFB_A7: S7.25, U8.1, V8.1
/S16B Ojects/LBUFB_A8: S7.26, U8.23, V8.23
/S16B Ojects/LBUFB_D0: S7.127, V8.9
/S16B Ojects/LBUFB_D1: S7.128, V8.10
/S16B Ojects/LBUFB_D2: S7.129, V8.11
/S16B Ojects/LBUFB_D3: S7.131, V8.13
/S16B Ojects/LBUFB_D4: S7.132, V8.14
/S16B Ojects/LBUFB_D5: S7.134, V8.15
/S16B Ojects/LBUFB_D6: S7.135, V8.16
/S16B Ojects/LBUFB_D7: S7.136, V8.17
/S16B Ojects/LBUFB_D8: S7.137, U8.9
/S16B Ojects/LBUFB_D9: S7.139, U8.10
/S16B Ojects/LBUFB_D10: S7.142, U8.11
/S16B Ojects/LBUFB_D11: S7.144, U8.13
/S16B Ojects/SHA1: S7.28, Y8.8, Z8.8
/S16B Ojects/SHA2: S7.29, Y8.7, Z8.7
/S16B Ojects/SHA3: S7.31, Y7.12, Y8.6, Z8.6
/S16B Ojects/SHA4: S7.32, Y7.9, Y8.5, Z8.5
/S16B Ojects/SHA5: S7.34, Y7.14, Y8.4, Z8.4
/S16B Ojects/SHA6: S7.35, Y7.7, Y8.3, Z8.3
/S16B Ojects/SHA7: S7.36, Y7.16, Y8.2, Z8.2
/S16B Ojects/SHA8: S7.37, Y7.5, Y8.1, Z8.1
/S16B Ojects/SHA9: S7.38, Y7.18, Y8.23, Z8.23
/S16B Ojects/SHA10: S7.39, Y7.3, Y8.22, Z8.22
/S16B Ojects/SHD0: S7.47, X7.18, X8.11, Z8.17
/S16B Ojects/SHD1: S7.46, X7.17, X8.8, Z8.16
/S16B Ojects/SHD2: S7.45, X7.16, X8.13, Z8.15
/S16B Ojects/SHD3: S7.44, X7.15, X8.6, Z8.14
/S16B Ojects/SHD4: S7.43, X7.14, X8.15, Z8.13
/S16B Ojects/SHD5: S7.42, X7.13, X8.4, Z8.11
/S16B Ojects/SHD6: S7.41, X7.12, X8.17, Z8.10
/S16B Ojects/SHD7: S7.40, X7.11, X8.2, Z8.9
/S16B Ojects/SHD8: S7.57, W7.18, W8.11, Y8.17
/S16B Ojects/SHD9: S7.56, W7.17, W8.8, Y8.16
/S16B Ojects/SHD10: S7.55, W7.16, W8.13, Y8.15
/S16B Ojects/SHD11: S7.54, W7.15, W8.6, Y8.14
/S16B Ojects/SHD12: S7.52, W7.14, W8.15, Y8.13
/S16B Ojects/SHD13: S7.51, W7.13, W8.4, Y8.11
/S16B Ojects/SHD14: S7.49, W7.12, W8.17, Y8.10
/S16B Ojects/SHD15: S7.48, W7.11, W8.2, Y8.9
/S16B Ojects/spriteram/~CEB: PRR8.15, U8.18, V8.18
/S16B Ojects/spriteram/~CEC: PRR8.14, RR8.18, S8.18
/S16B Ojects/~OEA: S7.154, Y8.20, Z8.20
/S16B Ojects/~OEC: RR8.20, S7.145, S8.20
/S16B Ojects/~OEH: S7.146, U8.20, V8.20
/S16B Ojects/~WEA: S7.153, Y8.21, Z8.21
/S16B Ojects/~WEH: S7.149, U8.21, V8.21
/S16B Ojects/~WEV: RR8.21, S7.147, S8.21
/S16B Scroll/BUFF_OE: Q1.1, Q1.19, Q2.1, Q2.19, W2.133
/S16B Scroll/CLK_SCRB: S3.11, W2.123
/S16B Scroll/FFSCR_~OE: S3.1, W2.124
/S16B Scroll/FF_OE: RR1.11, RR2.11, W2.134, X6.1, X6.19, Y6.1, Y6.19
/S16B Scroll/FF_~OE: RR1.1, RR2.1, W2.132
/S16B Scroll/LATCH_E: S1.11, W2.139, X4.20, Y4.20
/S16B Scroll/MAIN_ABB1: V4.8, W2.119, W4.8, X4.10, Y4.10, Y6.18
/S16B Scroll/MAIN_ABB2: V4.7, W2.118, W4.7, X4.9, Y4.9, Y6.16
/S16B Scroll/MAIN_ABB3: V4.6, W2.117, W4.6, X4.8, Y4.8, Y6.14
/S16B Scroll/MAIN_ABB4: V4.5, W2.116, W4.5, X4.7, Y4.7, Y6.12
/S16B Scroll/MAIN_ABB5: V4.4, W2.114, W4.4, X4.6, Y4.6, Y6.3
/S16B Scroll/MAIN_ABB6: V4.3, W2.113, W4.3, X4.5, Y4.5, Y6.5
/S16B Scroll/MAIN_ABB7: V4.2, W2.112, W4.2, X4.4, Y4.4, Y6.7
/S16B Scroll/MAIN_ABB8: V4.1, W2.111, W4.1, X4.3, Y4.3, Y6.9
/S16B Scroll/MAIN_ABB9: S1.7, V4.23, W2.109, W4.23, X6.9
/S16B Scroll/MAIN_ABB10: S1.14, V4.22, W2.108, W4.22, X6.7
/S16B Scroll/MAIN_ABB11: S1.13, V4.19, W2.107, W4.19, X6.5
/S16B Scroll/MAIN_ABB12: S1.8, W2.106, X6.12
/S16B Scroll/MAIN_ABB13: S1.4, W2.103, X6.14
/S16B Scroll/MAIN_ABB14: S1.17, W2.102, X6.16
/S16B Scroll/MAIN_ABB15: S1.3, W2.101, X6.18
/S16B Scroll/MAIN_DB'0: Q1.9, RR1.13, S3.3, W2.29, W4.9, X4.11
/S16B Scroll/MAIN_DB'1: Q1.12, RR1.8, S3.4, W2.28, W4.10, X4.12
/S16B Scroll/MAIN_DB'2: Q1.7, RR1.14, S3.7, W2.27, W4.11, X4.13
/S16B Scroll/MAIN_DB'3: Q1.14, RR1.7, S3.8, W2.26, W4.13, X4.15
/S16B Scroll/MAIN_DB'4: Q1.5, RR1.17, S3.13, W2.24, W4.14, X4.16
/S16B Scroll/MAIN_DB'5: Q1.16, RR1.4, S3.14, W2.23, W4.15, X4.17
/S16B Scroll/MAIN_DB'6: Q1.3, RR1.18, S3.17, W2.22, W4.16, X4.18
/S16B Scroll/MAIN_DB'7: Q1.18, RR1.3, S3.18, W2.21, W4.17, X4.19
/S16B Scroll/MAIN_DB'8: Q2.9, RR2.13, V4.9, W2.19, Y4.11
/S16B Scroll/MAIN_DB'9: Q2.12, RR2.8, V4.10, W2.18, Y4.12
/S16B Scroll/MAIN_DB'10: Q2.7, RR2.14, V4.11, W2.17, Y4.13
/S16B Scroll/MAIN_DB'11: Q2.14, RR2.7, V4.13, W2.16, Y4.15
/S16B Scroll/MAIN_DB'12: Q2.5, RR2.17, V4.14, W2.15, Y4.16
/S16B Scroll/MAIN_DB'13: Q2.16, RR2.4, V4.15, W2.14, Y4.17
/S16B Scroll/MAIN_DB'14: Q2.3, RR2.18, V4.16, W2.13, Y4.18
/S16B Scroll/MAIN_DB'15: Q2.18, RR2.3, V4.17, W2.12, Y4.19
/S16B Scroll/TMG_D~WR: V4.21, W2.142
/S16B Scroll/TMG~OEH: W2.138, X4.22, Y4.22
/S16B Scroll/TMG~OEL: V4.20, W2.143, W4.20
/S16B Scroll/tilemapg_ram/MAINABB'9: S1.6, X4.25, Y4.25
/S16B Scroll/tilemapg_ram/MAINABB'10: S1.15, X4.24, Y4.24
/S16B Scroll/tilemapg_ram/MAINABB'11: S1.12, X4.21, Y4.21
/S16B Scroll/tilemapg_ram/MAINABB'12: S1.9, X4.23, Y4.23
/S16B Scroll/tilemapg_ram/MAINABB'13: S1.5, X4.2, Y4.2
/S16B Scroll/tilemapg_ram/MAINABB'14: S1.16, X4.26, Y4.26
/S16B Scroll/tilemapg_ram/MAINABB'15: S1.2, X4.1, Y4.1
/S16B Scroll/~WE_A: W2.137, X4.27, Y4.27
/SCR_A0: A1.12, A2.12, A3.12, B1.12, B2.12, B3.12, W2.8
/SCR_A1: A1.11, A2.11, A3.11, B1.11, B2.11, B3.11, W2.9
/SCR_A2: A1.10, A2.10, A3.10, B1.10, B2.10, B3.10, W2.7
/SCR_A3: A1.9, A2.9, A3.9, B1.9, B2.9, B3.9, S3.2
/SCR_A4: A1.8, A2.8, A3.8, B1.8, B2.8, B3.8, S3.5
/SCR_A5: A1.7, A2.7, A3.7, B1.7, B2.7, B3.7, S3.6
/SCR_A6: A1.6, A2.6, A3.6, B1.6, B2.6, B3.6, S3.9
/SCR_A7: A1.5, A2.5, A3.5, B1.5, B2.5, B3.5, S3.12
/SCR_A8: A1.27, A2.27, A3.27, B1.27, B2.27, B3.27, S3.15
/SCR_A9: A1.26, A2.26, A3.26, B1.26, B2.26, B3.26, S3.16
/SCR_A10: A1.23, A2.23, A3.23, B1.23, B2.23, B3.23, S3.19
/SCR_A11: A1.25, A2.25, A3.25, B1.25, B2.25, B3.25, W2.4
/SCR_A12: A1.4, A2.4, A3.4, B1.4, B2.4, B3.4, W2.3
/SCR_A13: A1.28, A2.28, A3.28, B1.28, B2.28, B3.28, W2.2
/SCR_A14: A1.29, A2.29, A3.29, B1.29, B2.29, B3.29, W2.159
/SCR_A15: A1.3, A2.3, A3.3, B1.3, B2.3, B3.3, E4.4
/SCR_CLK: E8.26, E11.11, F11.11, Q10.2, W2.11
/SCR_D0: A1.13, B1.13, W2.71
/SCR_D1: A1.14, B1.14, W2.72
/SCR_D2: A1.15, B1.15, W2.73
/SCR_D3: A1.17, B1.17, W2.74
/SCR_D4: A1.18, B1.18, W2.76
/SCR_D5: A1.19, B1.19, W2.77
/SCR_D6: A1.20, B1.20, W2.78
/SCR_D7: A1.21, B1.21, W2.79
/SCR_D8: A2.13, B2.13, W2.82
/SCR_D9: A2.14, B2.14, W2.83
/SCR_D10: A2.15, B2.15, W2.84
/SCR_D11: A2.17, B2.17, W2.85
/SCR_D12: A2.18, B2.18, W2.86
/SCR_D13: A2.19, B2.19, W2.87
/SCR_D14: A2.20, B2.20, W2.88
/SCR_D15: A2.21, B2.21, W2.89
/SCR_D16: A3.13, B3.13, W2.91
/SCR_D17: A3.14, B3.14, W2.92
/SCR_D18: A3.15, B3.15, W2.93
/SCR_D19: A3.17, B3.17, W2.94
/SCR_D20: A3.18, B3.18, W2.96
/SCR_D21: A3.19, B3.19, W2.97
/SCR_D22: A3.20, B3.20, W2.98
/SCR_D23: A3.21, B3.21, W2.99
/SCR_SEL: E4.1, W2.158
/SND_A0: K4.30, L3.2
/SND_A1: K4.31, L3.4
/SND_A2: K4.32, L3.6
/SND_A3: K4.33, L3.8
/SND_A4: K4.34, L3.11
/SND_A5: K4.35, L3.13
/SND_A6: K4.36, L3.15
/SND_A7: K4.37, L3.17
/SND_A8: K4.38, M3.2
/SND_A9: K4.39, M3.4
/SND_A10: K4.40, M3.6
/SND_A11: K4.1, M3.8
/SND_A12: K4.2, M3.11
/SND_A13: K4.3, M3.13
/SND_A14: K4.4, M3.15
/SND_A15: K4.5, M3.17
/SND_AB0: E1.17, G1.17, K1.10, L3.18, Q4.10
/SND_AB1: E1.18, G1.18, K1.9, L3.16, Q4.9
/SND_AB2: K1.8, L3.14, Q4.8
/SND_AB3: K1.7, L3.12, Q4.7
/SND_AB4: H2.13, K1.3, L3.9, Q4.6
/SND_AB5: J3.1, K1.4, L3.7, Q4.5
/SND_AB6: J3.2, K1.5, L3.5, Q4.4
/SND_AB7: J3.3, K1.6, L3.3, Q4.3
/SND_AB8: K1.2, M3.18, Q4.25
/SND_AB9: K1.1, M3.16, Q4.24
/SND_AB10: K1.80, M3.14, Q4.21
/SND_AB11: K1.79, M3.12, Q4.23
/SND_AB12: K1.78, M3.9, Q4.2
/SND_AB13: J3.4, S4.4
/SND_AB14: J3.5, S4.7
/SND_AB15: J3.6, S4.9
/SND_CLK: PALR11.15, Q11.3
/SND_DB0: A4.13, B4.13, B5.13, B6.13, E1.2, G1.2, K1.28, K2.18, N9.25, Q4.11, RR4.3
/SND_DB1: A4.14, B4.14, B5.14, B6.14, E1.3, G1.3, K1.27, K2.17, N9.26, Q4.12, RR4.4
/SND_DB2: A4.15, B4.15, B5.15, B6.15, E1.4, G1.4, K1.26, K2.16, N9.27, Q4.13, RR4.7
/SND_DB3: A4.17, B4.17, B5.17, B6.17, E1.5, G1.5, K1.25, K2.15, N9.28, Q4.15, RR4.8
/SND_DB4: A4.18, B4.18, B5.18, B6.18, E1.6, G1.6, K1.24, K2.14, N9.29, Q4.16, RR4.13
/SND_DB5: A4.19, B4.19, B5.19, B6.19, E1.7, G1.7, K1.23, K2.13, N9.30, Q4.17, RR4.14
/SND_DB6: A4.20, B4.20, B5.20, B6.20, E1.8, G1.8, K1.22, K2.12, N9.32, Q4.18, RR4.17
/SND_DB7: A4.21, B4.21, B5.21, B6.21, E1.9, G1.9, K1.21, K2.11, N9.33, Q4.19, RR4.18
/SND_~CE: A4.22, H2.4
/SPRPAL1: PRR8.1, S7.11, S7.12, W2.149
/SPRPAL7: PRR8.7, S7.5, W2.131
/SPRPAL9: PRR8.9, S7.7
/SRAM_~CS1: K11.20, L11.20, N9.73
/SYNC: IC67.11, Q10.5
/Sound/CPU/~PCM: J3.12, S4.1, T4.1
/Sound/FM~CS: H2.15, J3.19, U4.2
/Sound/PCM/RAMA0: F2.10, G2.10, K1.76
/Sound/PCM/RAMA1: F2.9, G2.9, K1.75
/Sound/PCM/RAMA2: F2.8, G2.8, K1.74
/Sound/PCM/RAMA3: F2.7, G2.7, K1.73
/Sound/PCM/RAMA4: F2.6, G2.6, K1.68
/Sound/PCM/RAMA5: F2.5, G2.5, K1.67
/Sound/PCM/RAMA6: F2.4, G2.4, K1.66
/Sound/PCM/RAMA7: F2.3, G2.3, K1.65
/Sound/PCM/RAMA8: F2.25, G2.25, K1.59
/Sound/PCM/RAMA9: F2.24, G2.24, K1.58
/Sound/PCM/RAMA10: F2.21, G2.21, K1.57
/Sound/PCM/RAMA11: F2.23, G2.23, K1.56
/Sound/PCM/RAMA12: F2.2, G2.2, K1.55
/Sound/PCM/RAMA13: F2.26, G2.26, K1.54
/Sound/PCM/RAMA14: F2.1, G2.1, K1.53
/Sound/PCM/RAMD0: F2.11, G2.11, K1.51
/Sound/PCM/RAMD1: F2.12, G2.12, K1.50
/Sound/PCM/RAMD2: F2.13, G2.13, K1.49
/Sound/PCM/RAMD3: F2.15, G2.15, K1.48
/Sound/PCM/RAMD4: F2.16, G2.16, K1.47
/Sound/PCM/RAMD5: F2.17, G2.17, K1.46
/Sound/PCM/RAMD6: F2.18, G2.18, K1.45
/Sound/PCM/RAMD7: F2.19, G2.19, K1.44
/Sound/PCM/~CE_1: G2.20, K1.60
/Sound/PCM/~CE_2: F2.20, K1.61
/Sound/PCM/~OE: F2.22, G2.22, K1.62
/Sound/PCM/~WE: F2.27, G2.27, K1.63
/Sound/PCM~CE: H2.1, J3.13
/Sound/SND_AB13': M3.7, S4.2
/Sound/SND_AB14': M3.5, S4.5
/Sound/SND_AB15': M3.3, S4.11
/Sound/SND_D0: K2.2, K4.14
/Sound/SND_D1: K2.3, K4.15
/Sound/SND_D2: K2.4, K4.12
/Sound/SND_D3: K2.5, K4.8
/Sound/SND_D4: K2.6, K4.7
/Sound/SND_D5: K2.7, K4.9
/Sound/SND_D6: K2.8, K4.10
/Sound/SND_D7: K2.9, K4.13
/Sound/SND_~RST: D7.3, E1.11, G1.11, K1.64, K4.26, RR4.1, U4.1, U4.13
/Sound/amplifier/AVCC: IC92.4, IC93.4
/Sound/~FM0_CS: G1.14, H2.10
/Sound/~FM1_CS: E1.14, H2.12
/Sound/~INT: E1.13, K4.16
/Sound/~IORD: E1.16, G1.16, G4.8
/Sound/~IORQ: G4.10, G4.13, J3.8, K4.20
/Sound/~IOWR: E1.15, G1.15, G4.11, J3.11
/Sound/~M1: J3.7, K4.27
/Sound/~MRD: G4.3, K1.13, Q4.22
/Sound/~MREQ: G4.2, G4.5, J3.9, K4.19
/Sound/~MWR: G4.6, K1.14, Q4.27
/Sound/~RD: G4.1, G4.9, K2.1, K4.21
/Sound/~SBANK: J3.18, RR4.11
/Sound/~SNDRAM: J3.14, Q4.20
/Sound/~SND_WR: G4.4, G4.12, K4.22
/Sound/~WAIT: E7.6, K4.24
/TILEMAP0: F11.3, W2.65
/TILEMAP1: F11.7, W2.66
/TILEMAP3: E11.7, W2.62
/TILEMAP4: E11.13, W2.63
/VDP_A/B: PD11.12, V10.40
/VDP_EN: D6.64, PD11.1
/VDP_MCK: L10.11, Q10.11, V10.52
/VDP_~VSYNC: PALR11.3, V10.41
/VDP_~YS: PD11.13, V10.39
/VDP~DTAK: N9.36, V10.114
/VDP~RESET: Q11.9, S10.9, S11.2, T10.9, T11.2, V10.47
/VIDEOEN: D6.63, D7.4, PD11.2
/Video Sync/COUN_TCA: T10.15, T11.3
/Video Sync/COUN_TCB: S10.15, S11.3
/Video Sync/VS: PALR11.13, T10.2, T11.1
/Video Sync/XTAL_CLK: PALR11.1, Q10.12
/Video Sync/~HB: PALR11.4, T11.17
/~AS: H7.6, N9.96, V10.110
/~BERR: H7.22, N9.110
/~BGACK: H7.12, N9.102, N9.114
/~BG: H7.11, N9.101
/~BLANK: D7.6, E8.27
/~BR: H7.13, N9.103
/~CSYNC: S11.19, V10.42
/~DTACK: H7.10, N9.100
/~GRAY: D6.4, E8.2
/~HS: PRR8.8, S7.4, S10.2, S11.1, T10.1, T11.4, W2.144
/~IPL0: H7.25, N9.113
/~IPL1: H7.24, N9.112
/~IPL2: H7.23, N9.111
/~LDS: H7.8, N9.98, V10.112
/~MRST: D6.76, D7.1, F6.1, K11.26, L11.26, N9.37, W2.151
/~NMI: K4.17, N9.62
/~PAL: BB9.19, C11.1, C11.19, D9.19, D11.1, D11.19, N9.48, W2.61
/~RESET: P11.8, PALR11.2, Q11.12, Q11.13
/~RST_CLK: PALR11.17, Q11.11
/~SA: F11.13, W2.64
/~SHADE: E8.29, W2.59
/~UDS: H7.7, N9.97, V10.111
/~VDP_MIX: F6.11, F7.3
/~VPA: H7.21, N9.109
/~VS: C11.11, M6.12, N9.38, S10.1, S11.4, W2.145
unnamed: E11.2, E11.4
unnamed: E11.6, E11.8
unnamed: E11.12, E11.14
unnamed: E11.16, E11.18
unnamed: F7.1, F7.6
unnamed: F11.2, F11.4
unnamed: F11.6, F11.8
unnamed: F11.12, F11.14
unnamed: F11.16, F11.18
unnamed: H2.2, T4.12
unnamed: H2.3, T4.9
unnamed: IC69.8, V10.1
unnamed: IC69.9, V10.2
unnamed: IC69.4, V10.3
unnamed: IC69.5, V10.4
unnamed: IC70.8, V10.5
unnamed: IC70.9, V10.6
unnamed: IC70.4, V10.7
unnamed: IC70.5, V10.8
unnamed: IC92.5, IC92.10
unnamed: IC92.13, IC92.14
unnamed: IC93.3, IC93.12
unnamed: IC93.1, IC93.2
unnamed: IC93.7, IC93.10
unnamed: IC93.8, IC93.9
unnamed: IC93.13, IC93.14
unnamed: E7.1, J3.15
unnamed: L10.2, L10.6
unnamed: L10.12, PALR11.12
unnamed: L10.9, PALR11.6
unnamed: Q11.2, Q11.6
unnamed: RR4.2, S4.3
unnamed: RR4.5, S4.6
unnamed: RR4.6, S4.10
unnamed: RR4.9, S4.13
unnamed: RR4.12, T4.3
unnamed: RR4.15, T4.6
unnamed: RR4.16, T4.10
unnamed: RR4.19, T4.13
unnamed: S10.14, S11.6
unnamed: S10.13, S11.7
unnamed: S10.12, S11.8
unnamed: S10.11, S11.9
unnamed: S11.5, T11.18
unnamed: T10.14, T11.6
unnamed: T10.13, T11.7
unnamed: T10.12, T11.8
unnamed: T10.11, T11.9
unnamed: E7.2, U4.5
unnamed: E7.8, U4.11
unnamed: E7.5, U4.9
unnamed: E7.3, E7.4, U4.10
unnamed: D7.5, W2.157
VCC: A1.1, A1.31, A1.32, A2.1, A2.31, A2.32, A3.1, A3.31, A3.32, A4.1, A4.31, A4.32, A5.1, A5.31, A5.32, A6.1, A6.31, A6.32, A8.1, A8.31, A8.32, A9.1, A9.31, A9.32, A10.1, A10.31, A10.32, A11.1, A11.31, A11.32, B1.1, B1.31, B1.32, B2.1, B2.31, B2.32, B3.1, B3.31, B3.32, B4.1, B4.31, B4.32, B5.1, B5.31, B5.32, B6.1, B6.31, B6.32, B8.1, B8.31, B8.32, B9.1, B9.31, B9.32, B10.1, B10.31, B10.32, B11.1, B11.31, B11.32, BB8.24, C8.24, C11.20, D6.16, D6.41, D6.65, D6.91, D11.20, E1.22, E1.23, E7.12, E8.8, E8.24, F2.28, G1.22, G1.23, G2.28, G11.20, H7.14, H7.49, H11.20, IC66.14, IC67.14, IC69.18, IC70.18, J3.20, J11.20, K1.12, K1.19, K1.43, K1.69, K4.11, K11.28, L3.20, L10.1, L10.4, L10.10, L10.13, L11.28, M3.20, M6.40, N9.14, N9.34, N9.44, N9.74, N9.104, P11.5, P11.6, PALR11.20, PD11.20, PRR8.20, Q1.20, Q2.20, Q4.26, Q4.28, Q10.16, Q11.1, Q11.4, Q11.10, RR8.24, S1.20, S7.20, S7.60, S7.80, S7.100, S7.140, S7.155, S7.160, S8.24, S10.7, S10.10, S11.20, T10.7, T10.10, T11.20, U4.4, U8.24, V4.24, V8.24, V10.30, V10.54, V10.94, V10.128, W2.20, W2.41, W2.60, W2.80, W2.100, W2.120, W2.126, W2.140, W2.160, W4.24, W8.20, X4.28, X6.20, X8.20, Y4.28, Y6.20, Y7.20, Y8.24, Z8.24
VSS: A1.16, A2.16, A3.16, A4.2, A4.16, A5.16, A6.16, A7.9, A7.11, A7.13, A7.15, A8.16, A8.24, A9.16, A9.24, A10.16, A10.24, A11.16, A11.24, AA4.9, AA4.11, AA4.13, AA4.15, AA5.9, AA5.11, AA5.13, AA5.15, AA6.9, AA6.11, AA6.13, AA6.15, AA8.9, AA8.11, AA8.13, AA8.15, AA9.9, AA9.11, AA9.13, AA9.15, AA11.19, B1.16, B1.24, B2.16, B2.24, B3.16, B3.24, B4.16, B4.24, B5.16, B5.24, B6.16, B6.24, B7.1, B7.13, B7.15, B8.16, B8.24, B9.16, B9.24, B10.16, B10.24, B11.16, B11.24, BB8.12, BB8.18, BB8.20, C8.12, C8.18, C8.20, C11.10, D6.6, D6.15, D6.25, D6.40, D6.56, D6.66, D6.75, D6.90, D11.10, E1.1, E1.12, E1.19, E4.15, E8.16, E8.17, E8.32, E11.1, F2.14, F11.1, G1.1, G1.12, G1.19, G2.14, G11.1, G11.10, G11.19, H2.14, H7.16, H7.53, H9.19, H11.1, H11.10, H11.19, IC66.7, IC67.7, IC69.6, IC70.6, IC92.11, IC93.11, IC94.3, IC94.7, J3.10, J11.1, J11.10, J11.19, K1.15, K1.16, K1.17, K1.18, K1.52, K1.72, K2.19, K4.29, K9.19, K11.14, L3.1, L3.10, L3.19, L11.14, M3.1, M3.10, M3.19, M6.20, M6.31, N9.1, N9.15, N9.31, N9.35, N9.39, N9.45, N9.61, N9.75, N9.91, N9.105, P11.2, P11.4, PALR11.10, PALR11.11, PD11.10, PRR8.10, Q1.10, Q2.10, Q4.14, Q10.1, Q10.8, Q10.15, RR8.12, RR8.19, RR8.22, S1.1, S1.10, S4.14, S4.15, S7.10, S7.30, S7.50, S7.67, S7.70, S7.90, S7.110, S7.130, S7.150, S8.12, S8.19, S8.22, S10.3, S10.4, S10.5, S10.6, S11.10, S11.11, T4.2, T4.5, T4.11, T4.14, T4.15, T10.3, T10.4, T10.5, T10.6, T11.10, T11.11, U4.12, U8.12, U8.19, U8.22, V4.12, V4.18, V8.12, V8.19, V8.22, V10.17, V10.26, V10.96, V10.97, W2.1, W2.10, W2.30, W2.50, W2.67, W2.70, W2.81, W2.90, W2.110, W2.121, W2.127, W2.130, W2.150, W4.12, W4.18, W8.10, X4.14, X6.10, X6.17, X8.10, Y4.14, Y6.10, Y7.10, Y8.12, Y8.18, Y8.19, Z8.12, Z8.18, Z8.19
